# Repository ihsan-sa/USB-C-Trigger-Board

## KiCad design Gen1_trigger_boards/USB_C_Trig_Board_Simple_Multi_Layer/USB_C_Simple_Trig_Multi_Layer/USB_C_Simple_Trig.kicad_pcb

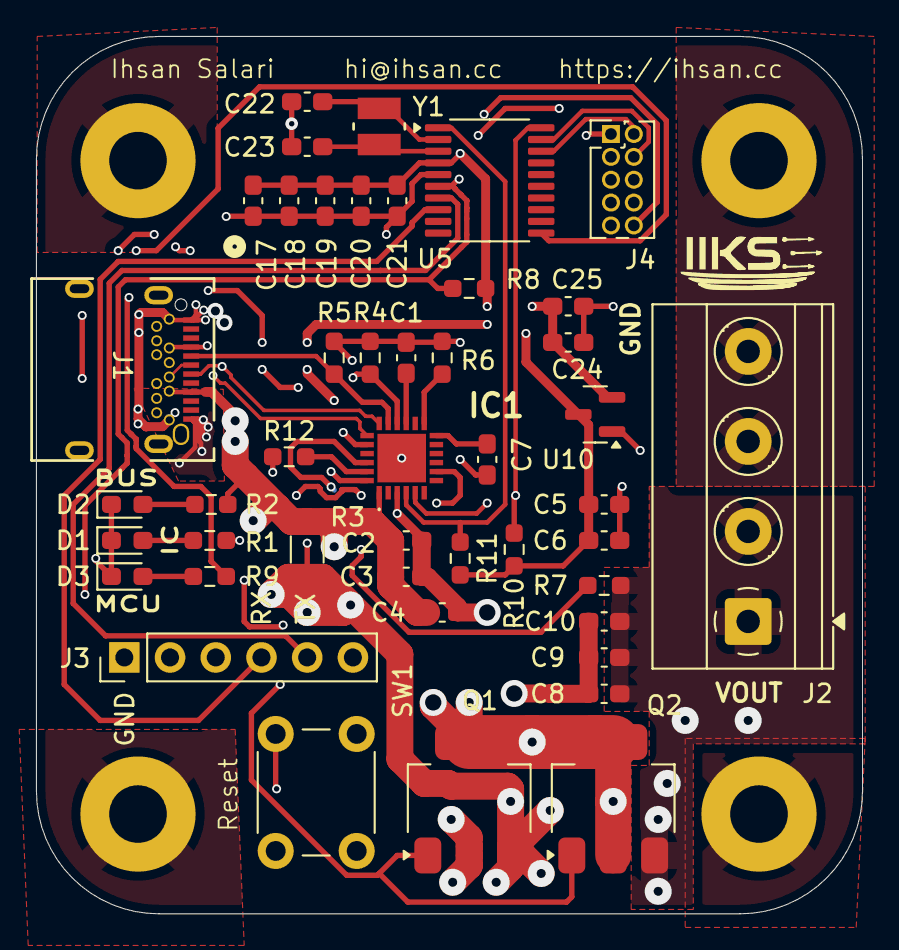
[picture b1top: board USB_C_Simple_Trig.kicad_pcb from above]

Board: 6 copper layers, 45.9 x 48.7 mm, 49 parts (0 on the bottom side), 31 nets.

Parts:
C1, C4, C6, C7, C10, C19, C20, C25: 100n; C_0603_1608Metric_Pad1.08x0.95mm_HandSolder
C2, C8: 10u; C_0603_1608Metric_Pad1.08x0.95mm_HandSolder
C3, C5, C9, C17, C18, C24: 1u; C_0603_1608Metric_Pad1.08x0.95mm_HandSolder
C21: 10n; C_0603_1608Metric_Pad1.08x0.95mm_HandSolder
C22, C23: *; C_0603_1608Metric_Pad1.08x0.95mm_HandSolder
D1, D2, D3: LED; LED_0603_1608Metric_Pad1.05x0.95mm_HandSolder
H1, H2, H3, H4: MountingHole_Pad; MountingHole_3.2mm_M3_Pad
IC1: AP33772SDKZ-13-FA01; AP33772SDKZ13FA01
J1: USB_C_Receptacle; CONN24_4056-03-A_GCT
J2: Screw_Terminal_01x04; TerminalBlock_Phoenix_MKDS-1,5-4_1x04_P5.00mm_Horizontal
J3: Conn_01x06_Pin; PinHeader_1x06_P2.54mm_Vertical
J4: Conn_ARM_JTAG_SWD_10; PinHeader_2x05_P1.27mm_Vertical
Q1, Q2: BUK7880-55A/CUX; SOT-223-3_TabPin2
R1, R9: 1k; R_0603_1608Metric_Pad0.98x0.95mm_HandSolder
R2: 100k; R_0603_1608Metric_Pad0.98x0.95mm_HandSolder
R3: 5m; R_1206_3216Metric_Pad1.30x1.75mm_HandSolder
R4, R5: 5.1k; R_0603_1608Metric_Pad0.98x0.95mm_HandSolder
R6, R8: 10k; R_0603_1608Metric_Pad0.98x0.95mm_HandSolder
R7: 100; R_0603_1608Metric_Pad0.98x0.95mm_HandSolder
R10, R11: *; R_0603_1608Metric_Pad0.98x0.95mm_HandSolder
R12: 10; R_0603_1608Metric_Pad0.98x0.95mm_HandSolder
SW1: SW_Push; SW_PUSH_6mm
U5: STM32C011F6Px; TSSOP-20_4.4x6.5mm_P0.65mm
U10: AP2127N-3.3; SOT-23
Y1: CG04874-8M; XTAL_CG04874_NDK

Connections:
+1V8: C7.1, IC1.12 (V18)
+3V3: C17.1, C18.1, C19.1, C20.1, C21.1, C24.1, C25.1, J4.1 (VTref), R8.1, U5.4 (VDD), U10.2 (VO)
+5V: C5.1, C6.1, IC1.20 (V5V), R10.1, R11.1, U10.3 (VI)
/MCU/I2C_SCL: IC1.5 (SCL), R10.2, U5.20 (PB6)
/MCU/I2C_SDA: IC1.4 (SDA), R11.2, U5.1 (PB7)
/MCU/NRST: J4.10 (~RESET), R8.2, SW1.2, U5.6 (PF2)
/MCU/OSC_IN: C22.2, U5.2 (PC14), Y1.2
/MCU/OSC_OUT: C23.2, U5.3 (PC15), Y1.1
/MCU/STATUS_LED: R9.2, U5.11 (PA4)
/MCU/SWCLK: J4.4 (SWCLK/TCK), U5.19 (PA14)
/MCU/SWDIO: J4.2 (SWDIO/TMS), U5.18 (PA13)
/MCU/UART_RX: J3.4, U5.8 (PA1)
/MCU/UART_TX: J3.5, U5.7 (PA0)
/USB_C_IC/CC1: IC1.17 (CC1), J1.A5 (CC1), R5.2
/USB_C_IC/CC2: IC1.16 (CC2), J1.B5 (CC2), R4.2
/USB_C_IC/PWR_EN: IC1.23 (PWR_EN), R12.2
/USB_C_IC/data_+: IC1.19 (DP), J1.A6 (D+), J1.B6 (D+)
/USB_C_IC/data_-: IC1.18 (DN), J1.A7 (D-), J1.B7 (D-)
GND: C1.2, C2.2, C3.2, C4.2, C5.2, C6.2, C7.2, C8.2, C9.2, C10.2, C17.2, C18.2, C19.2, C20.2, C21.2, C22.1, C23.1, C24.2, C25.2, D1.1 (K), D2.1 (K), D3.1 (K), H1.1, H2.1, H3.1, H4.1, IC1.3 (GND_1), IC1.25 (GND_2), J1.A1 (GND), J1.A12 (GND), J1.B1 (GND), J1.B12 (GND), J2.3, J2.4, J3.1, J4.3 (GND), J4.5 (GND), J4.9 (GNDDetect), R4.1, R5.1, R6.2, SW1.1, U5.5 (VSS), U10.1 (GND)
unnamed: D1.2 (A), R1.1
unnamed: D2.2 (A), R2.2
unnamed: D3.2 (A), R9.1
unnamed: C1.1, IC1.15 (IFB)
unnamed: IC1.8 (LED), R1.2
unnamed: IC1.13 (OTP), R6.1
unnamed: IC1.24 (VCC), Q1.3 (S), R3.2
unnamed: IC1.22 (VOUT), R7.1
unnamed: Q1.1 (D), Q2.1 (D)
unnamed: Q1.2 (G), Q2.2 (G), R12.1
VBUS: C2.1, C3.1, C4.1, IC1.1 (ISENP), J1.A4 (VBUS), J1.A9 (VBUS), J1.B4 (VBUS), J1.B9 (VBUS), R2.1, R3.1
VOUT: C8.1, C9.1, C10.1, J2.1, J2.2, Q2.3 (S), R7.2

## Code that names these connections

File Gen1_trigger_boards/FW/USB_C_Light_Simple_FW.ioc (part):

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Mcu.Name=STM32C011F(4-6)Px
Mcu.Package=TSSOP20
Mcu.UserName=STM32C011F6Px
PA0.Mode=Asynchronous
PA0.Signal=USART1_TX
PA1.Mode=Asynchronous
PA1.Signal=USART1_RX
PA13.Mode=Serial_Wire
PA13.Signal=DEBUG_SWDIO
PA14-BOOT0.Mode=Serial_Wire
PA14-BOOT0.Signal=DEBUG_SWCLK
PA4.GPIOParameters=GPIO_ModeDefaultPP,PinState
PA4.GPIO_ModeDefaultPP=GPIO_MODE_AF_PP
PA4.PinState=GPIO_PIN_SET
PA4.Signal=S_TIM14_CH1
PB6.Mode=I2C
PB6.Signal=I2C1_SCL
PB7.Mode=I2C
PB7.Signal=I2C1_SDA
PC14-OSCX_IN\ (PC14).Mode=HSE-External-Oscillator-REMAPPED
PC14-OSCX_IN\ (PC14).Signal=RCC_OSCX_IN
PC15-OSCX_OUT\ (PC15).Mode=HSE-External-Oscillator-REMAPPED
PC15-OSCX_OUT\ (PC15).Signal=RCC_OSCX_OUT
RCC.HSE_VALUE=8000000
RCC.SYSCLKFreq_VALUE=12000000
board=custom

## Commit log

2025-07-13 Fleshed out high level overview and created and nearly completed USB IC schematic.
2025-07-22 Simple trigger board: placed all the components. Next step: route
2025-07-24 Simple trigger board: finished draft PCB routing
2025-08-16 USB-C Multi-layer SimpleTrig
    Created project and completed first version of multi-layer setup.
2025-08-16 Simple 2-Layer Trig:
    Rerouted power traces and added some high current copper pour on ground plane.
2025-08-16 Silkscreen update for both simple trig boards.
2025-08-19 ordered v1
2025-09-14 Created folder for Gen1 trigger boards
2025-09-14 Moved trigger boards to new folder
